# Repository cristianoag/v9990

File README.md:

# v9990
My attempt to implement the Yamaha v9990 in Verilog HDL.

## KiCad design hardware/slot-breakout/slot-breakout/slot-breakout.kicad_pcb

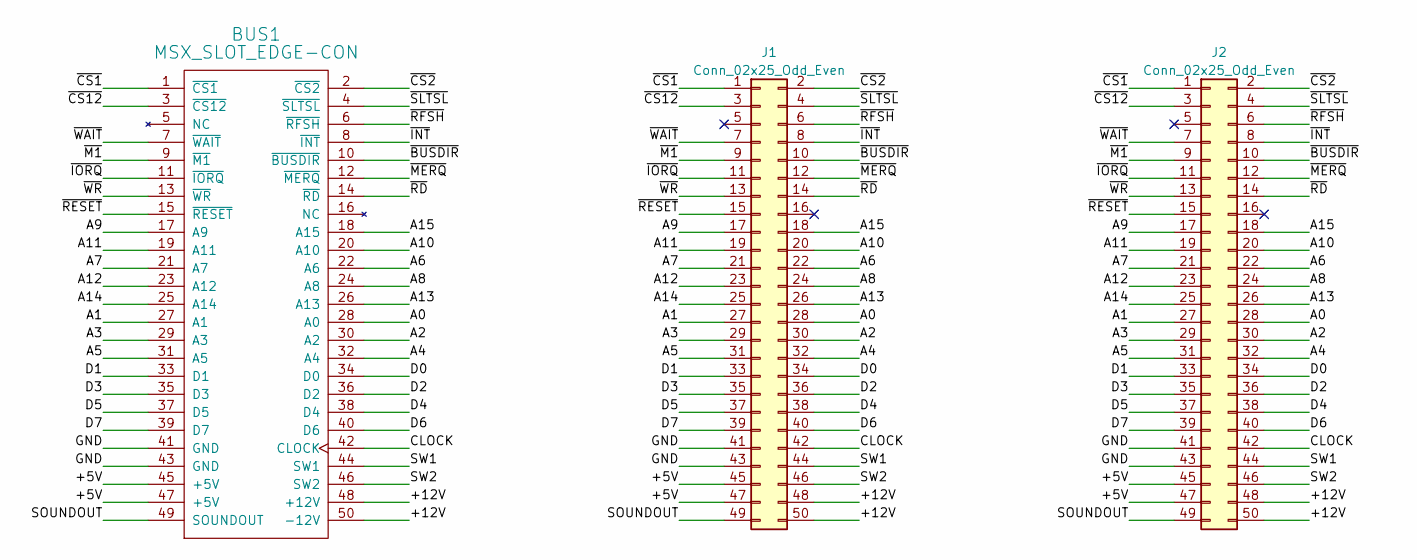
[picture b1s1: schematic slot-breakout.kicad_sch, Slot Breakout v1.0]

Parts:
BUS1: MSX_SLOT_EDGE-CON; msx_cartridge; MPN n/a
J1, J2: Conn_02x25_Odd_Even; PinHeader_2x25_P2.54mm_Vertical

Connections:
/+5V: BUS1.45 (+5V), BUS1.47 (+5V), J1.45, J1.47, J2.45, J2.47
/+12V: BUS1.48 (+12V), BUS1.50 (-12V), J1.48, J1.50, J2.48, J2.50
/A0: BUS1.28 (A0), J1.28, J2.28
/A1: BUS1.27 (A1), J1.27, J2.27
/A2: BUS1.30 (A2), J1.30, J2.30
/A3: BUS1.29 (A3), J1.29, J2.29
/A4: BUS1.32 (A4), J1.32, J2.32
/A5: BUS1.31 (A5), J1.31, J2.31
/A6: BUS1.22 (A6), J1.22, J2.22
/A7: BUS1.21 (A7), J1.21, J2.21
/A8: BUS1.24 (A8), J1.24, J2.24
/A9: BUS1.17 (A9), J1.17, J2.17
/A10: BUS1.20 (A10), J1.20, J2.20
/A11: BUS1.19 (A11), J1.19, J2.19
/A12: BUS1.23 (A12), J1.23, J2.23
/A13: BUS1.26 (A13), J1.26, J2.26
/A14: BUS1.25 (A14), J1.25, J2.25
/A15: BUS1.18 (A15), J1.18, J2.18
/CLOCK: BUS1.42 (CLOCK), J1.42, J2.42
/D0: BUS1.34 (D0), J1.34, J2.34
/D1: BUS1.33 (D1), J1.33, J2.33
/D2: BUS1.36 (D2~), J1.36, J2.36
/D3: BUS1.35 (D3), J1.35, J2.35
/D4: BUS1.38 (D4), J1.38, J2.38
/D5: BUS1.37 (D5), J1.37, J2.37
/D6: BUS1.40 (D6), J1.40, J2.40
/D7: BUS1.39 (D7), J1.39, J2.39
/GND: BUS1.41 (GND), BUS1.43 (GND), J1.41, J1.43, J2.41, J2.43
/SOUNDOUT: BUS1.49 (SOUNDOUT), J1.49, J2.49
/SW1: BUS1.44 (SW1), J1.44, J2.44
/SW2: BUS1.46 (SW2), J1.46, J2.46
/~BUSDIR: BUS1.10 (~BUSDIR), J1.10, J2.10
/~CS1: BUS1.1 (~CS1), J1.1, J2.1
/~CS2: BUS1.2 (~CS2), J1.2, J2.2
/~CS12: BUS1.3 (~CS12), J1.3, J2.3
/~INT: BUS1.8 (~INT), J1.8, J2.8
/~IORQ: BUS1.11 (~IORQ), J1.11, J2.11
/~M1: BUS1.9 (~M1), J1.9, J2.9
/~MERQ: BUS1.12 (~MERQ), J1.12, J2.12
/~RD: BUS1.14 (~RD), J1.14, J2.14
/~RESET: BUS1.15 (~RESET), J1.15, J2.15
/~RFSH: BUS1.6 (~RFSH), J1.6, J2.6
/~SLTSL: BUS1.4 (~SLTSL), J1.4, J2.4
/~WAIT: BUS1.7 (~WAIT), J1.7, J2.7
/~WR: BUS1.13 (~WR), J1.13, J2.13

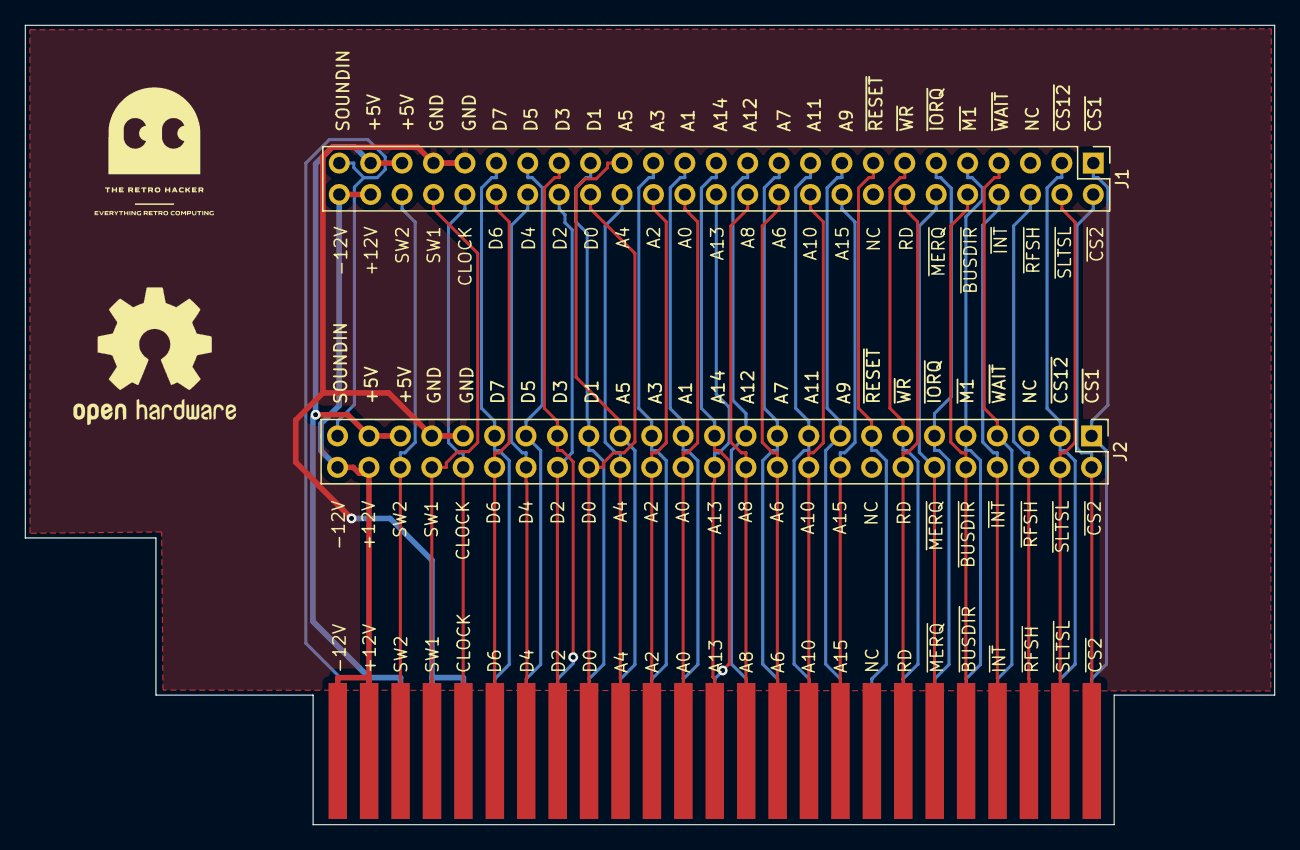
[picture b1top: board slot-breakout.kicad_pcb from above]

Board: 2 copper layers, 101.0 x 64.6 mm, 3 parts (0 on the bottom side), 45 nets.

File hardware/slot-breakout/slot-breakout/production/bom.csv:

Designator,Footprint,Quantity,Value,LCSC Part #
"J1, J2",PinHeader_2x25_P2.54mm_Vertical,2,Conn_02x25_Odd_Even,

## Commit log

2022-07-09 Initial push. Documentation.
2023-04-22 cartridge slot breakboard
